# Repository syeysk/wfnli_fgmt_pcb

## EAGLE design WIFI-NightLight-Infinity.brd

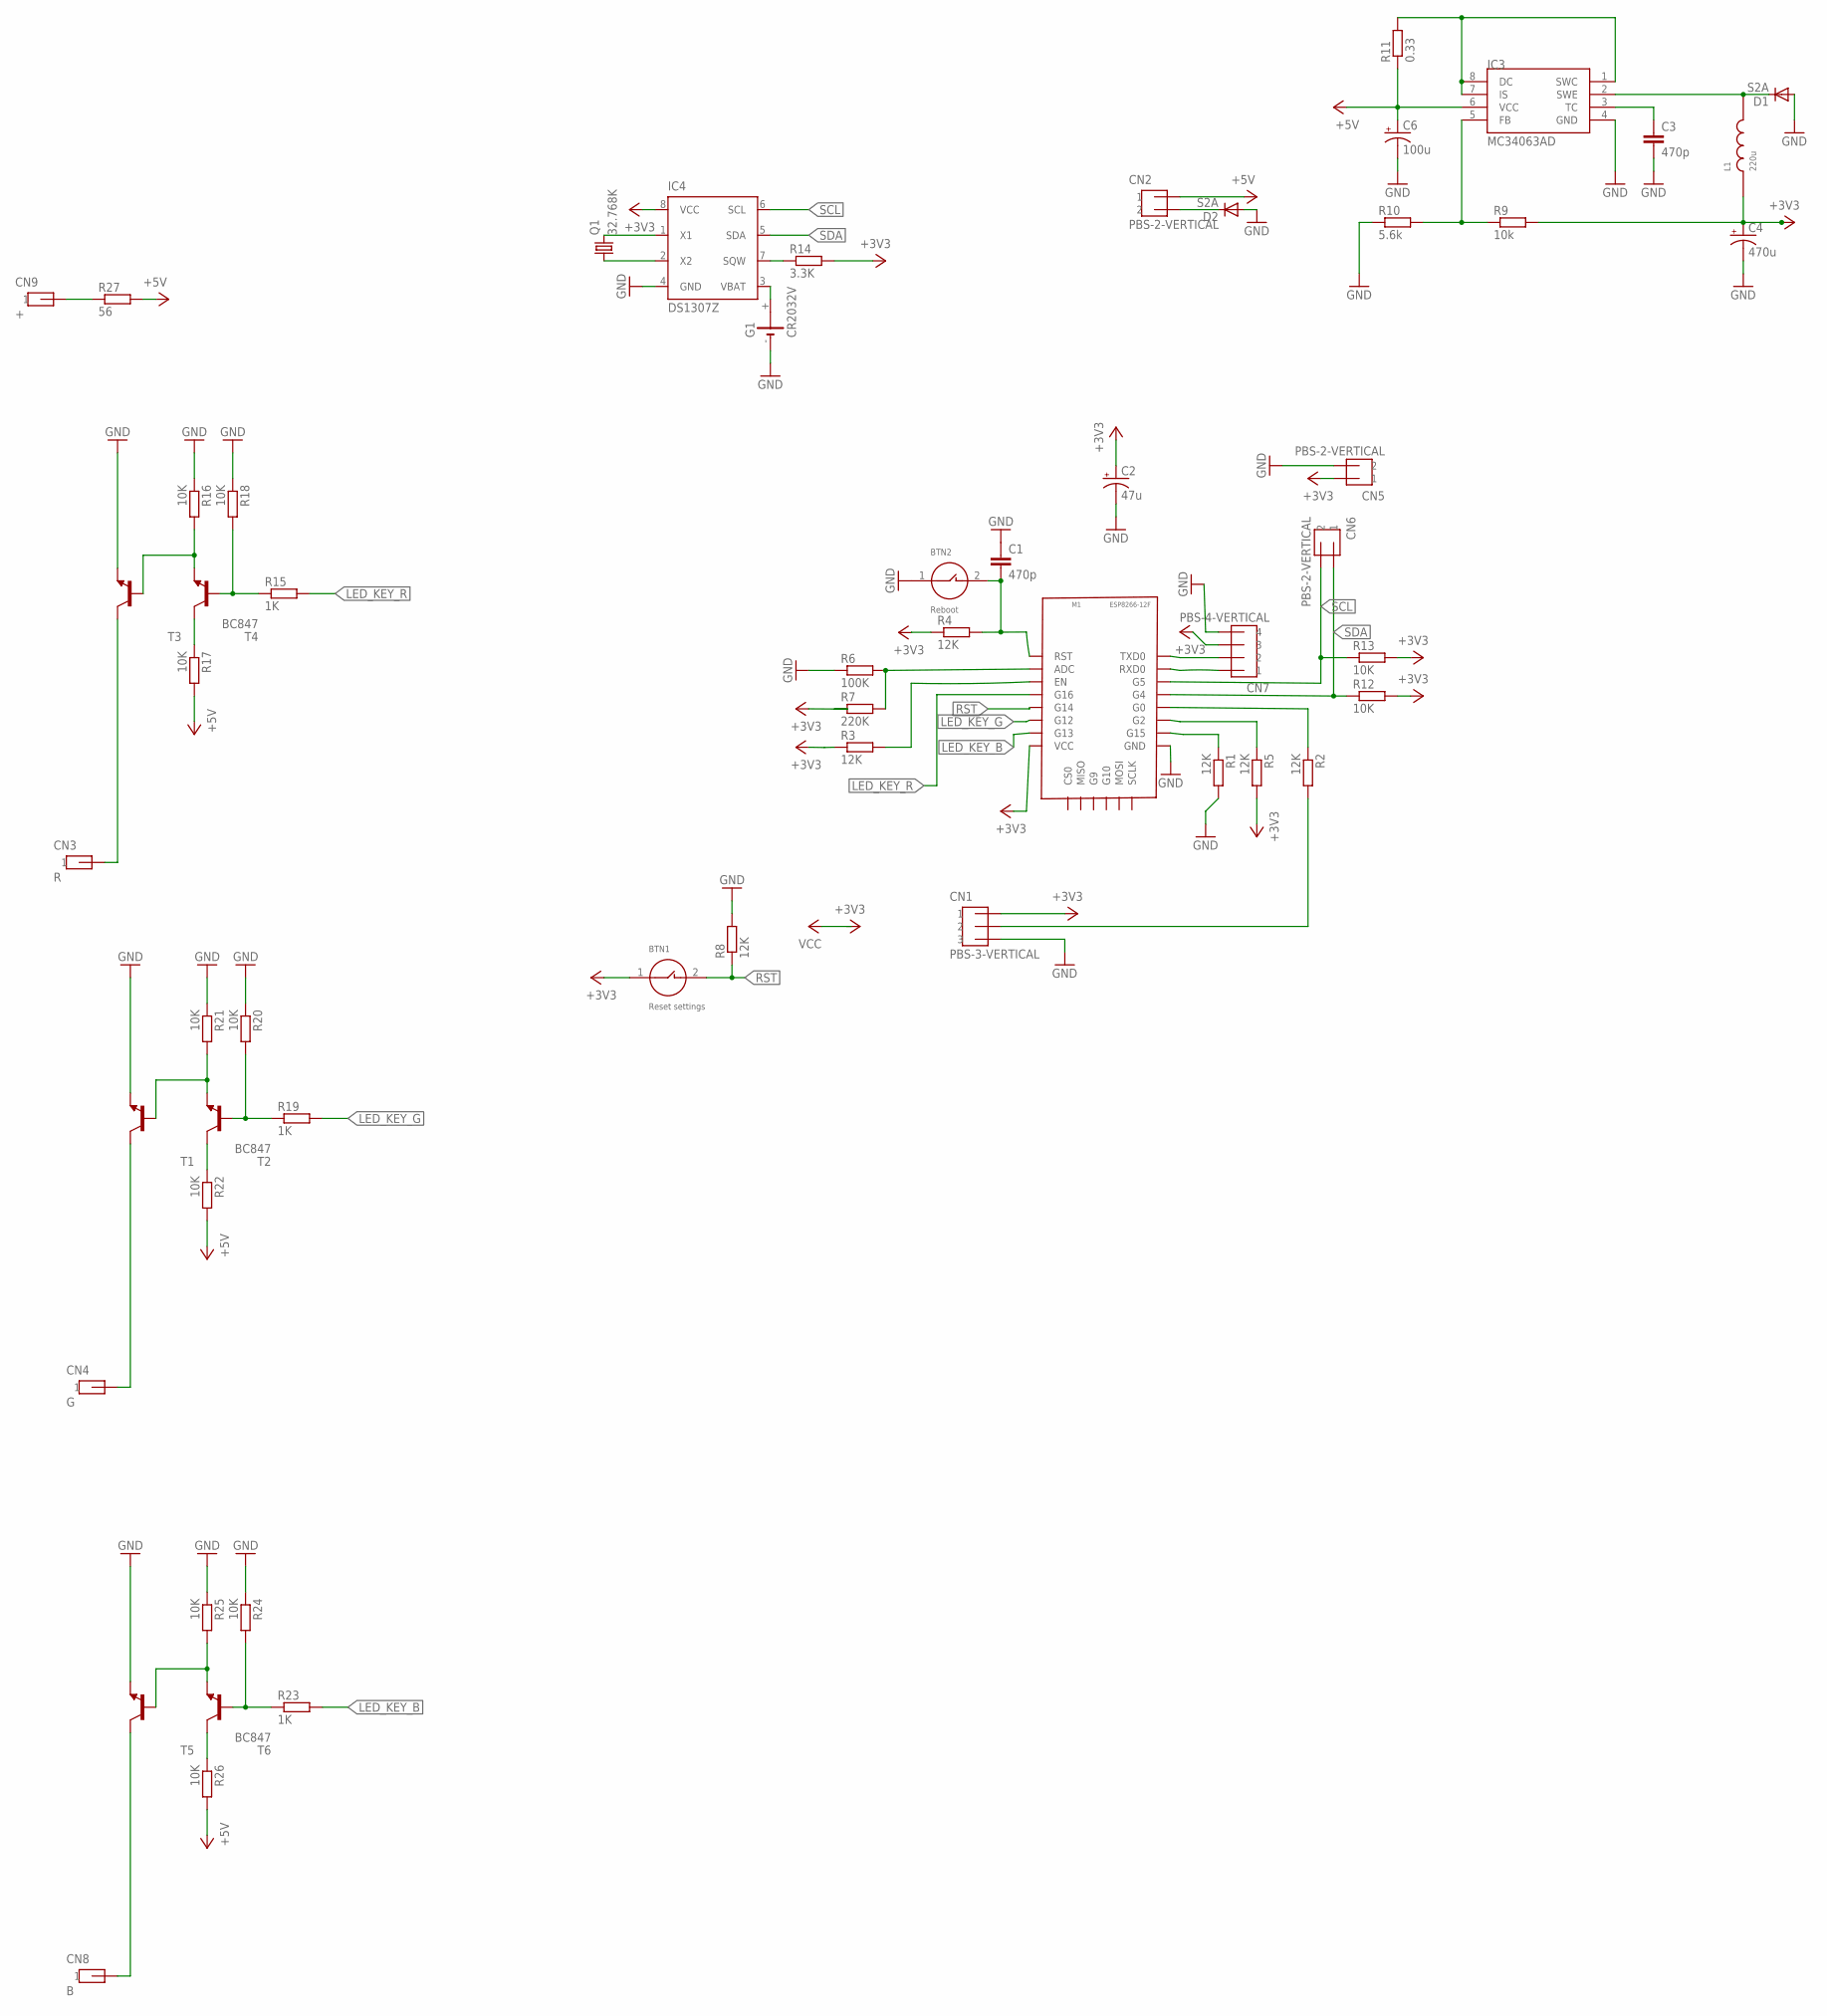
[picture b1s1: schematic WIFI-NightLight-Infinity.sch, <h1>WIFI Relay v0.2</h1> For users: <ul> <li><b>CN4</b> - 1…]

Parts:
BTN1: Reset settings; BTN-6X4-SMD
BTN2: Reboot; BTN-6X4-SMD
C1, C3: 470p; C0603
C2: 47u; CT3216
C4: 470u; D/7343-31W
C6: 100u; D/7343-31W
CN1: PBS-3-VERTICAL
CN2, CN5, CN6: PBS-2-VERTICAL
CN3: R; PBS-1-VERTICAL
CN4: G; PBS-1-VERTICAL
CN7: PBS-4-VERTICAL
CN8: B; PBS-1-VERTICAL
CN9: +; PBS-1-VERTICAL
D1, D2: S2A; DO214AA
G1: CR2032V
IC3: MC34063AD; SOIC8
IC4: DS1307Z; SOIC8
L1: 220u; INDUCTOR-5-10
M1: ESP8266-12F
Q1: 32.768K; TC38H
R1, R2, R3, R4, R5, R8: 12K; R0603
R6: 100K; R0603
R7: 220K; R0603
R9: 10k; R0603
R10: 5.6k; R0603
R11: 0.33; R0603
R12, R13, R16, R17, R18, R20, R21, R22, R24, R25, R26: 10K; R0603
R14: 3.3K; R0603
R15, R19, R23: 1K; R0603
R27: 56; 0411/12
T1, T3, T5: -NPN-TO126V; TO126V
T2, T4, T6: BC847; SOT23

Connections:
+3V3: BTN1.1, C2.- (+), C4.+, CN1.P$1 (1), CN5.P$1 (1), CN7.P$3 (3), IC4.8 (VCC), L1.P$1 (1), M1.VCC, R3.1, R4.1, R5.2, R7.1, R9.2, R12.2, R13.2, R14.2
+5V: C6.+, CN2.P$1 (1), IC3.6 (VCC), R11.1, R17.2, R22.2, R26.2, R27.2
GND: BTN2.1, C1.1, C2.+ (-), C3.2, C4.-, C6.-, CN1.P$3 (3), CN5.P$2 (2), CN7.P$4 (4), D1.A, D2.A, G1.-, IC3.4 (GND), IC4.4 (GND), M1.GND, R1.2, R6.1, R8.2, R10.1, R16.1, R18.1, R20.1, R21.1, R24.1, R25.1, T1.1 (E), T3.1 (E), T5.1 (E)
LED_KEY_B: M1.G13, R23.2
LED_KEY_G: M1.G12, R19.2
LED_KEY_R: M1.G16, R15.2
unnamed: M1.G15, R1.1
unnamed: M1.G2, R5.1
unnamed: M1.G0, R2.1
unnamed: CN1.P$2 (2), R2.2
unnamed: M1.EN, R3.2
unnamed: CN7.P$1 (1), M1.RXD0
unnamed: CN7.P$2 (2), M1.TXD0
unnamed: R15.1, R18.2, T4.1 (B)
unnamed: R16.2, T3.3 (B), T4.2 (E)
unnamed: R17.1, T4.3 (C)
unnamed: R19.1, R20.2, T2.1 (B)
unnamed: CN3.P$1, T3.2 (C)
unnamed: R21.2, T1.3 (B), T2.2 (E)
unnamed: R22.1, T2.3 (C)
unnamed: CN4.P$1, T1.2 (C)
unnamed: R23.1, R24.2, T6.1 (B)
unnamed: R25.2, T5.3 (B), T6.2 (E)
unnamed: R26.1, T6.3 (C)
unnamed: CN8.P$1, T5.2 (C)
unnamed: CN9.P$1, R27.1
unnamed: BTN2.2, C1.2, M1.RST, R4.2
unnamed: IC4.1 (X1), Q1.2
unnamed: IC4.2 (X2), Q1.1
unnamed: M1.ADC, R6.2, R7.2
unnamed: IC3.5 (FB), R9.1, R10.2
unnamed: D1.C, IC3.2 (SWE), L1.P$2
unnamed: IC3.1 (SWC), IC3.7 (IS), IC3.8 (DC), R11.2
unnamed: C3.1, IC3.3 (TC)
unnamed: CN2.P$2 (2), D2.C
unnamed: IC4.7 (SQW), R14.1
unnamed: G1.+, IC4.3 (VBAT)
RST: BTN1.2, M1.G14, R8.1
SCL: CN6.P$2 (2), IC4.6 (SCL), M1.G5, R13.1
SDA: CN6.P$1 (1), IC4.5 (SDA), M1.G4, R12.1

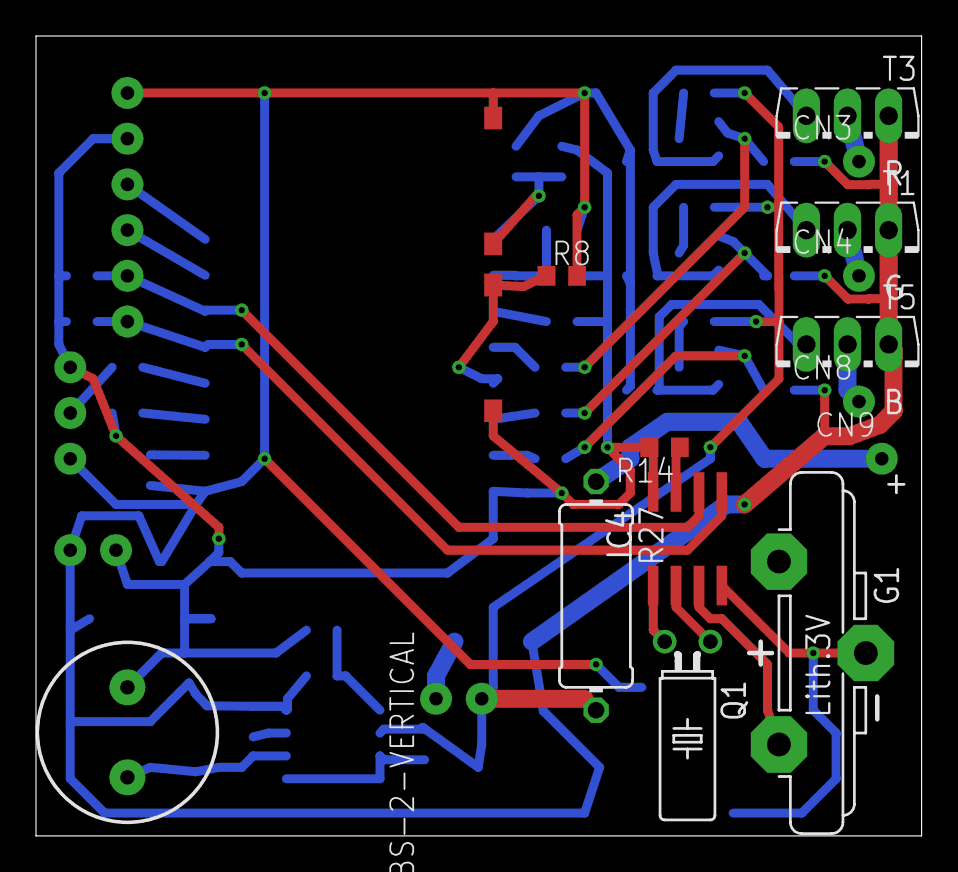
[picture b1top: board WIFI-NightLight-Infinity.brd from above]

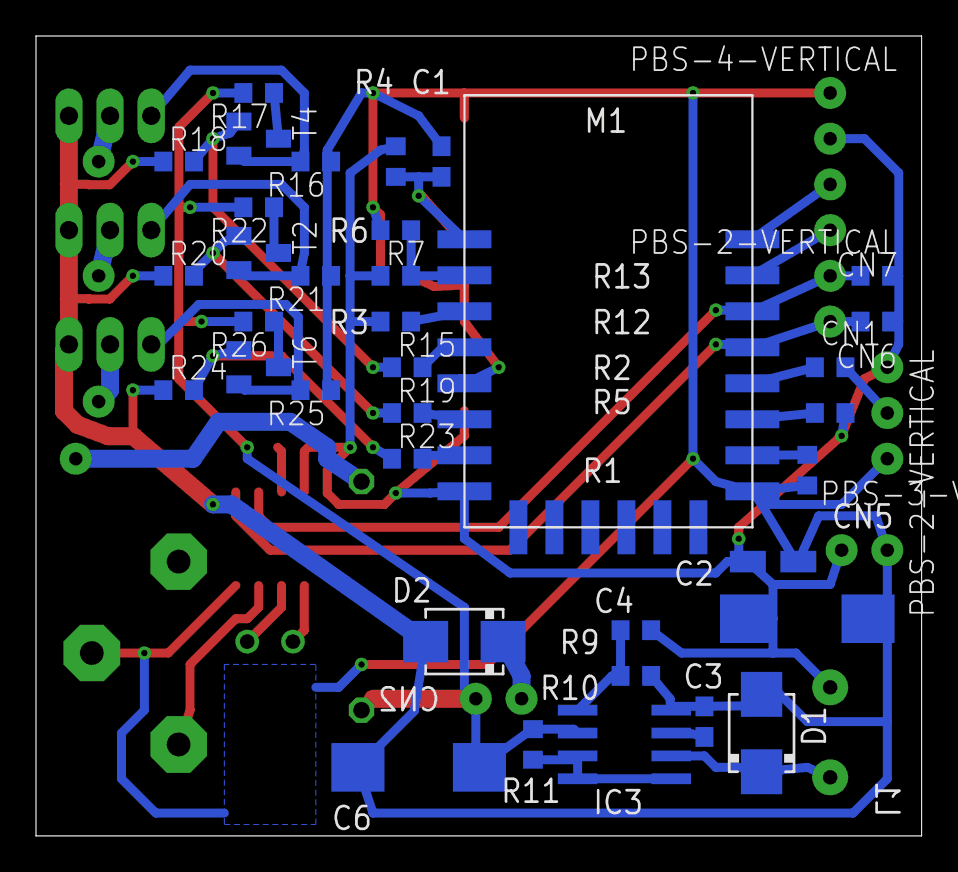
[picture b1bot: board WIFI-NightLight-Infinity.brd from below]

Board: 2 copper layers, 49.2 x 44.4 mm, 57 parts (40 on the bottom side), 40 nets.

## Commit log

2018-09-15 transistors were aaded
2018-09-15 Scheme for all led-channels have done
2018-09-18 Resistor was added for plus of LED-strip
2018-09-18 Errors were fixed
2018-09-20 submodule with eagle libs was added
2018-09-20 Preparing for production.
2018-10-14 Value was changed. Updating for Eagle 9.2.0
